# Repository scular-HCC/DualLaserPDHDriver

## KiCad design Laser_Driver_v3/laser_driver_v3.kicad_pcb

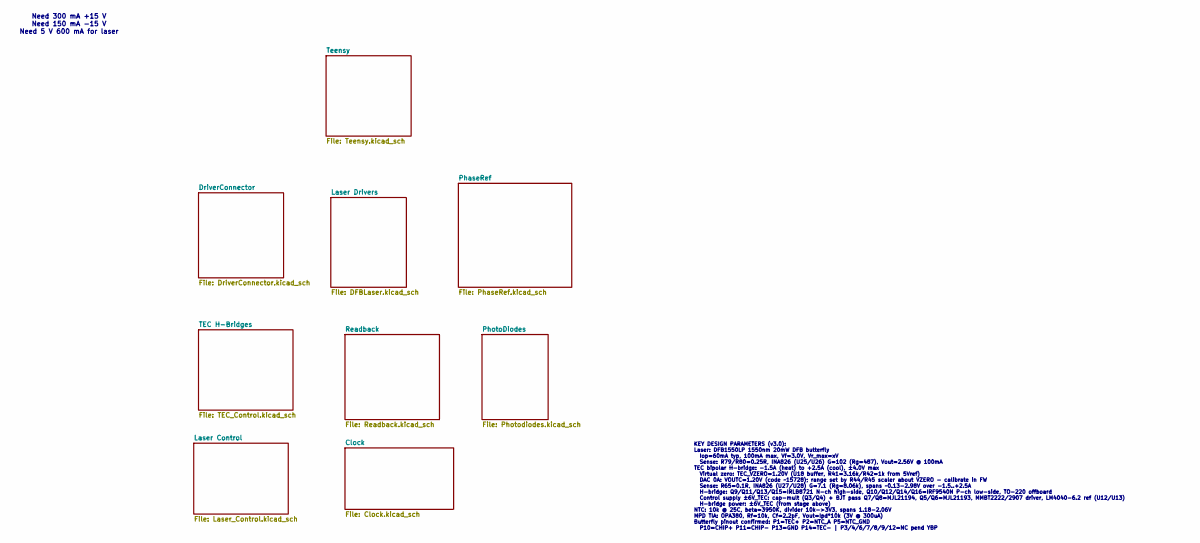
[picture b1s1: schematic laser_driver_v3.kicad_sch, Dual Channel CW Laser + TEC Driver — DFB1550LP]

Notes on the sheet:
Need 300 mA +15 V Need 150 mA -15 V Need 5 V 600 mA for laser
KEY DESIGN PARAMETERS (v3.0): Laser: DFB1550LP 1550nm 20mW DFB butterfly Iop=60mA typ, 100mA max, Vf=3.0V, Vr_max=xV Sense: R79/R80=0.25R, INA826 (U25/U26) G=102 (Rg=487), Vout=2.56V @ 100mA TEC bipolar H-bridge: -1.5A (heat) to +2.5A (cool), ±4.0V max Virtual zero: TEC_VZERO=1.20V (U18 buffer, R41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

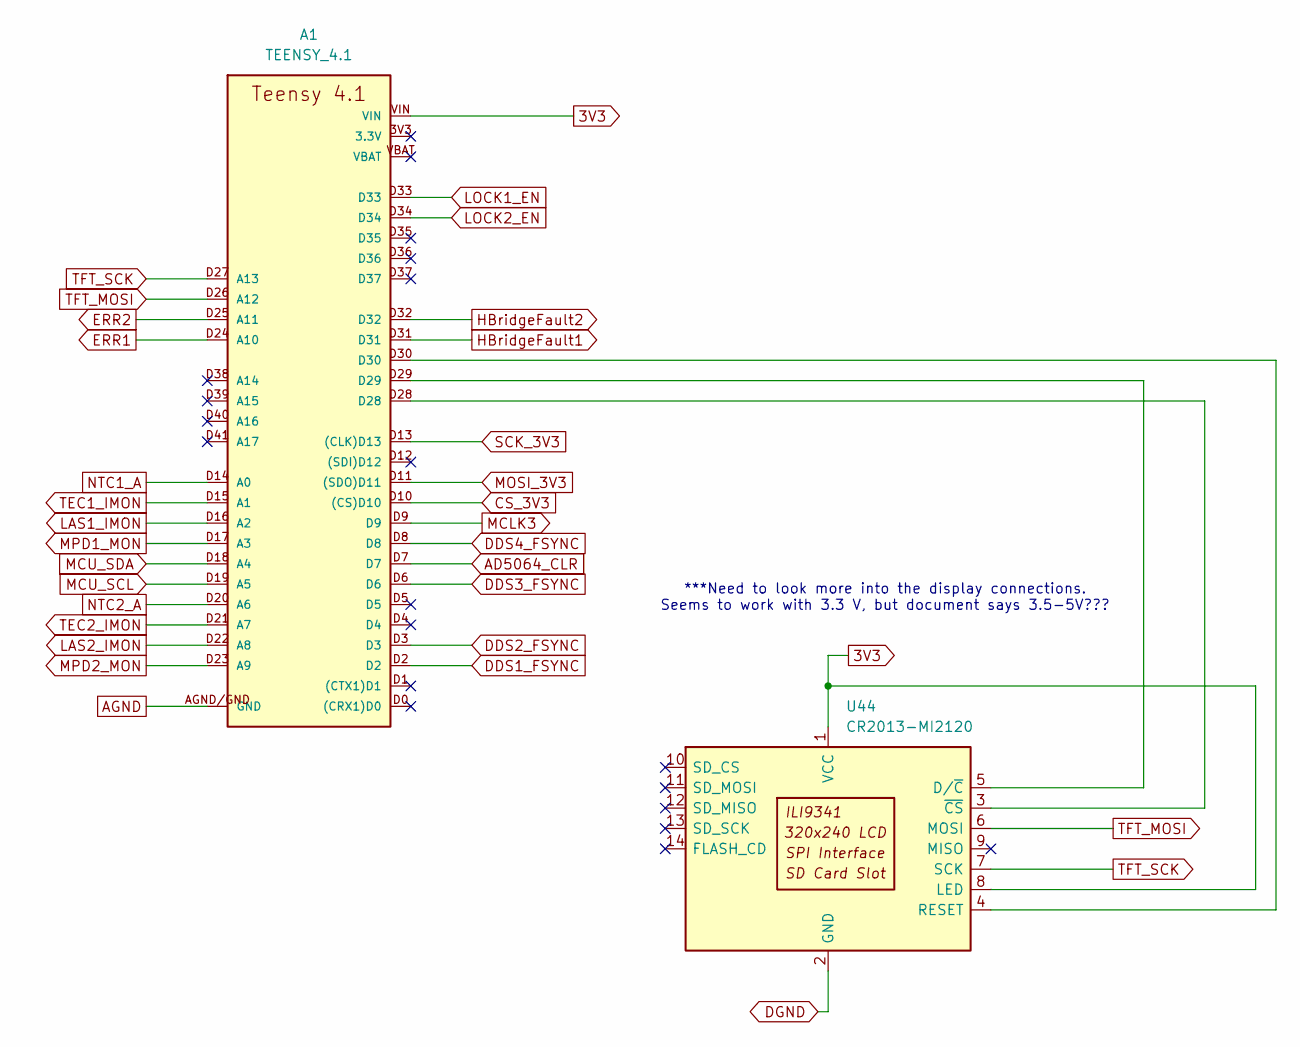
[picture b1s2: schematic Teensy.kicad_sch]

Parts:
A1: TEENSY_4.1; TEENSY_LONG_EXT
U44: CR2013-MI2120

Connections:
3V3: A1.VIN, U44.1 (VCC), U44.8 (LED); also elsewhere on the board
AD5064_CLR: A1.D7; also elsewhere on the board
AGND: A1.AGND/GND (GND), A1.GND, A1.GND@2 (GND); also elsewhere on the board
CS_3V3: A1.D10 ((CS)D10); also elsewhere on the board
DDS1_FSYNC: A1.D2; also elsewhere on the board
DDS2_FSYNC: A1.D3; also elsewhere on the board
DDS3_FSYNC: A1.D6; also elsewhere on the board
DDS4_FSYNC: A1.D8; also elsewhere on the board
DGND: U44.2 (GND); also elsewhere on the board
ERR1: A1.D24 (A10); also elsewhere on the board
ERR2: A1.D25 (A11); also elsewhere on the board
HBridgeFault1: A1.D31; also elsewhere on the board
HBridgeFault2: A1.D32; also elsewhere on the board
LAS1_IMON: A1.D16 (A2); also elsewhere on the board
LAS2_IMON: A1.D22 (A8); also elsewhere on the board
LOCK1_EN: A1.D33; also elsewhere on the board
LOCK2_EN: A1.D34; also elsewhere on the board
MCLK3: A1.D9; also elsewhere on the board
MCU_SCL: A1.D19 (A5); also elsewhere on the board
MCU_SDA: A1.D18 (A4); also elsewhere on the board
MOSI_3V3: A1.D11 ((SDO)D11); also elsewhere on the board
MPD1_MON: A1.D17 (A3); also elsewhere on the board
MPD2_MON: A1.D23 (A9); also elsewhere on the board
NTC1_A: A1.D14 (A0); also elsewhere on the board
NTC2_A: A1.D20 (A6); also elsewhere on the board
unnamed: A1.D29, U44.5 (D/~C)
unnamed: A1.D30, U44.4 (RESET)
unnamed: A1.D28, U44.3 (~CS)
SCK_3V3: A1.D13 ((CLK)D13); also elsewhere on the board
TEC1_IMON: A1.D15 (A1); also elsewhere on the board
TEC2_IMON: A1.D21 (A7); also elsewhere on the board
TFT_MOSI: A1.D26 (A12), U44.6 (MOSI)
TFT_SCK: A1.D27 (A13), U44.7 (SCK)

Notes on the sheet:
***Need to look more into the display connections. Seems to work with 3.3 V, but document says 3.5-5V???

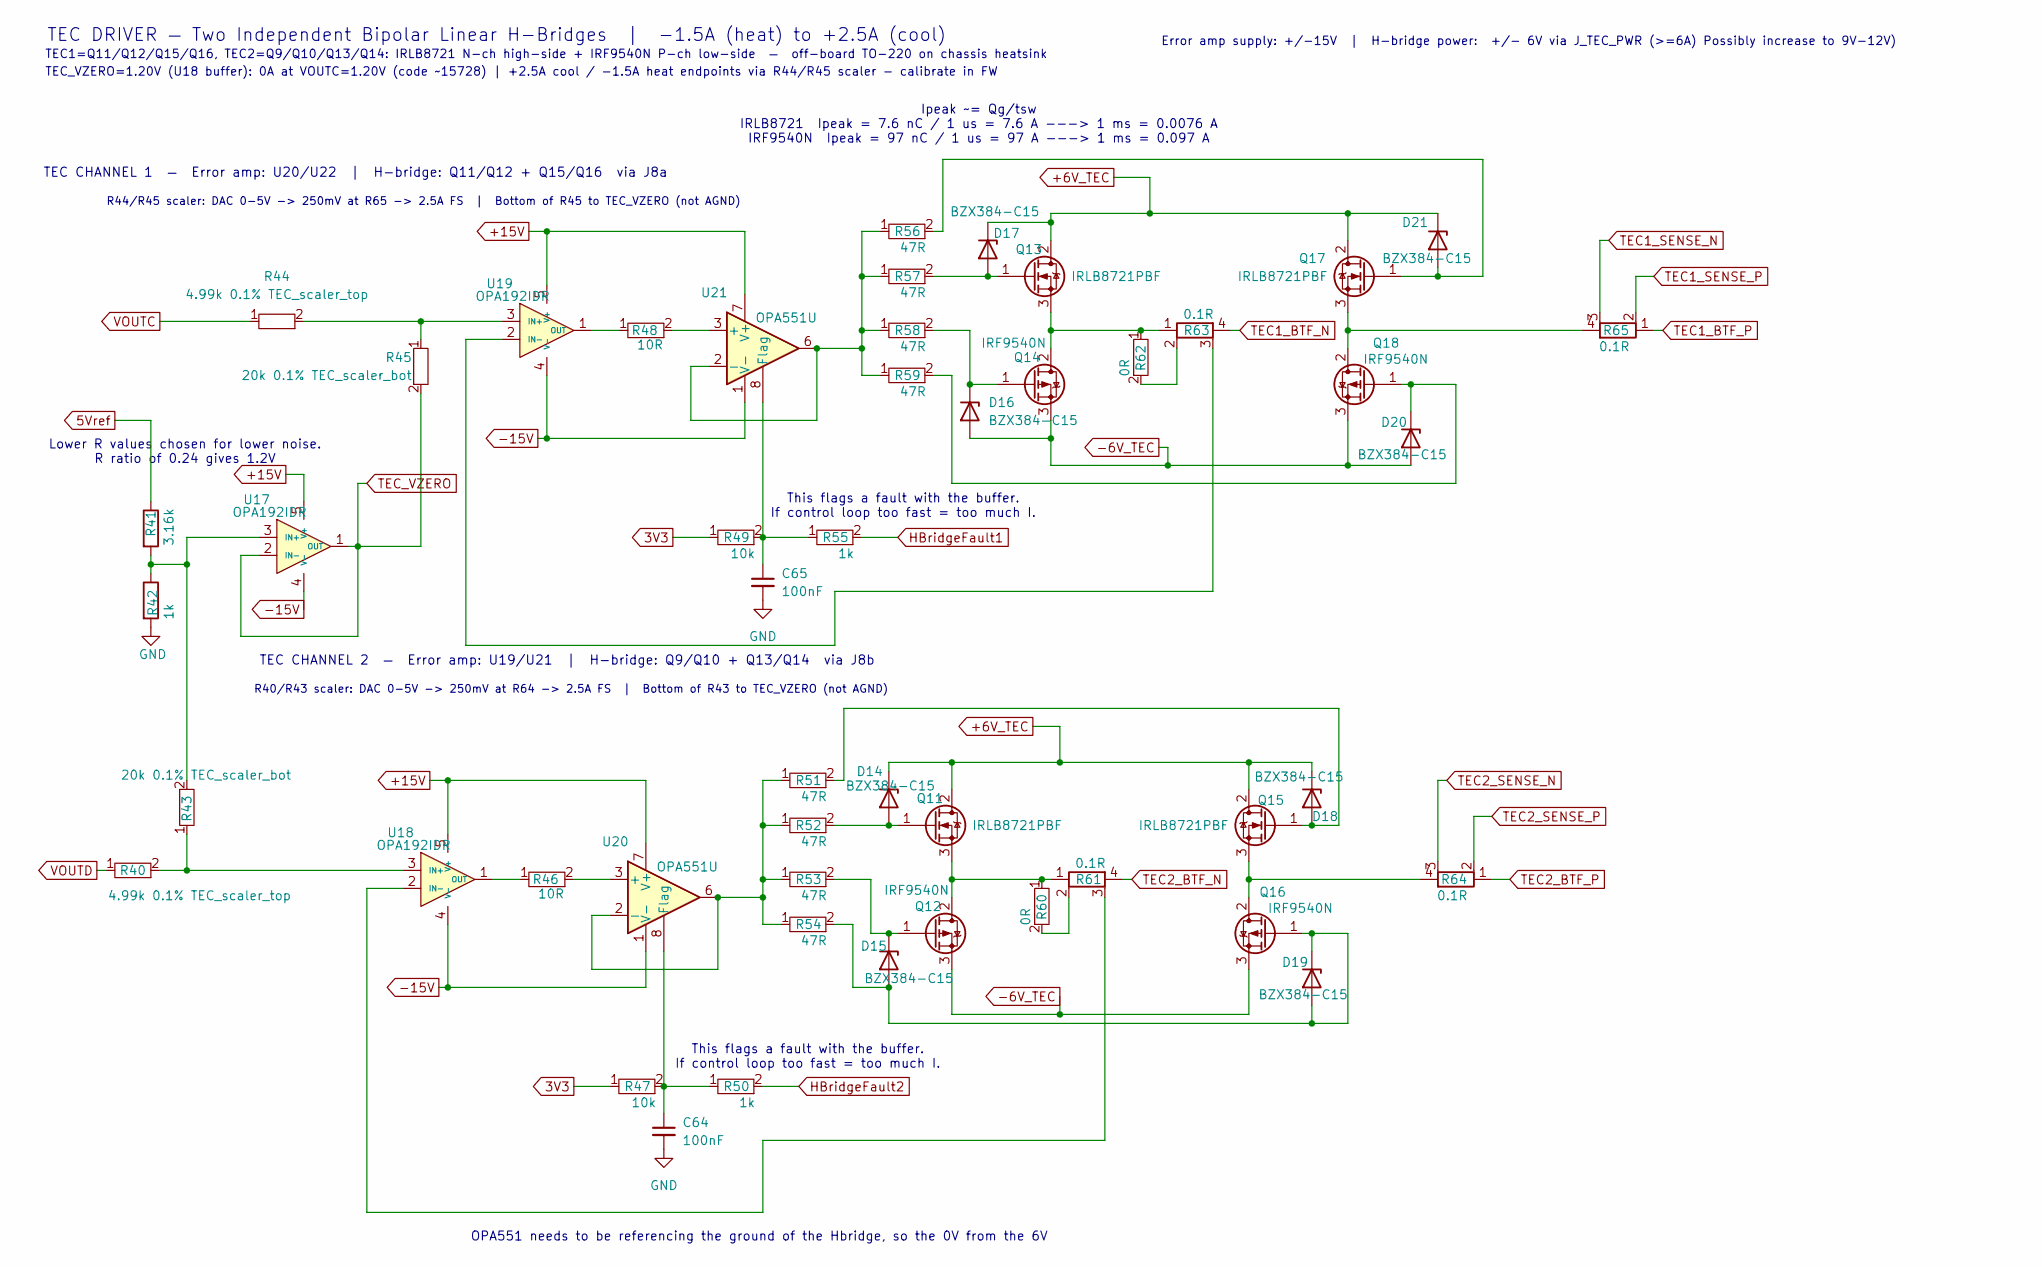
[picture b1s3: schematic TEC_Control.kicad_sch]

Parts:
C64, C65: 100nF; C_0805_2012Metric_Pad1.18x1.45mm_HandSolder
D14, D15, D16, D17, D18, D19, D20, D21: BZX384-C15; D_SOD-323
Q11, Q13, Q15, Q17: IRLB8721PBF; TO-220-3_Vertical
Q12, Q14, Q16, Q18: IRF9540N; TO-220-3_Vertical
R40, R44: 4.99k 0.1% TEC_scaler_top; R_0805_2012Metric
R41: 3.16k; R_0805_2012Metric_Pad1.20x1.40mm_HandSolder
R42, R50, R55: 1k; R_0805_2012Metric_Pad1.20x1.40mm_HandSolder
R43, R45: 20k 0.1% TEC_scaler_bot; R_0805_2012Metric
R46, R48: 10R; R_0805_2012Metric_Pad1.20x1.40mm_HandSolder
R47, R49: 10k; R_0805_2012Metric_Pad1.20x1.40mm_HandSolder
R51, R52, R53, R54, R56, R57, R58, R59: 47R; R_0805_2012Metric_Pad1.20x1.40mm_HandSolder
R60, R62: 0R; R_0805_2012Metric_Pad1.20x1.40mm_HandSolder
R61, R63, R64, R65: 0.1R; R_Shunt_Vishay_WSKW0612
U17, U18, U19: OPA192IDR; SOIC-8_3.9x4.9mm_P1.27mm
U20, U21: OPA551U; SOIC-8_3.9x4.9mm_P1.27mm

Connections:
3V3: R47.1, R49.1; also elsewhere on the board
5Vref: R41.1; also elsewhere on the board
+6V_TEC: D14.1 (K), D17.1 (K), D18.1 (K), D21.1 (K), Q11.2 (D), Q13.2 (D), Q15.2 (D), Q17.2 (D); also elsewhere on the board
+15V: U17.5 (V+), U18.5 (V+), U19.5 (V+), U20.7 (V+), U21.7 (V+); also elsewhere on the board
-6V_TEC: D16.2 (A), D20.2 (A), Q12.3 (S), Q14.3 (S), Q16.3 (S), Q18.3 (S); also elsewhere on the board
-15V: U17.4 (V-), U18.4 (V-), U19.4 (V-), U20.1 (V-), U20.4 (V-), U20.5 (V-), U21.1 (V-), U21.4 (V-), U21.5 (V-); also elsewhere on the board
GND: C64.2, C65.2, R42.2; also elsewhere on the board
HBridgeFault1: R55.2; also elsewhere on the board
HBridgeFault2: R50.2; also elsewhere on the board
unnamed: D14.2 (A), Q11.1 (G), R52.2
unnamed: D15.2 (A), D19.1 (K), D19.2 (A), Q16.1 (G), R54.2
unnamed: D15.1 (K), Q12.1 (G), R53.2
unnamed: D16.1 (K), Q14.1 (G), R58.2
unnamed: D17.2 (A), Q13.1 (G), R57.2
unnamed: D18.2 (A), Q15.1 (G), R51.2
unnamed: D20.1 (K), Q18.1 (G), R59.2
unnamed: D21.2 (A), Q17.1 (G), R56.2
unnamed: Q11.3 (S), Q12.2 (D), R60.1, R61.1
unnamed: Q13.3 (S), Q14.2 (D), R62.1, R63.1
unnamed: Q15.3 (S), Q16.2 (D), R64.4
unnamed: Q17.3 (S), Q18.2 (D), R65.4
unnamed: R60.2, R61.2
unnamed: R62.2, R63.2
unnamed: R41.2, R42.1, R43.2, U17.3 (IN+)
unnamed: R40.2, R43.1, U18.3 (IN+)
unnamed: R61.3, U18.2 (IN-)
unnamed: R46.1, U18.1 (OUT)
unnamed: R44.2, R45.1, U19.3 (IN+)
unnamed: R63.3, U19.2 (IN-)
unnamed: R48.1, U19.1 (OUT)
unnamed: R46.2, U20.3 (+)
unnamed: R51.1, R52.1, R53.1, R54.1, U20.2 (-), U20.6
unnamed: C64.1, R47.2, R50.1, U20.8 (Flag)
unnamed: R48.2, U21.3 (+)
unnamed: R56.1, R57.1, R58.1, R59.1, U21.2 (-), U21.6
unnamed: C65.1, R49.2, R55.1, U21.8 (Flag)
TEC1_BTF_N: R63.4; also elsewhere on the board
TEC1_BTF_P: R65.1; also elsewhere on the board
TEC1_SENSE_N: R65.3; also elsewhere on the board
TEC1_SENSE_P: R65.2; also elsewhere on the board
TEC2_BTF_N: R61.4; also elsewhere on the board
TEC2_BTF_P: R64.1; also elsewhere on the board
TEC2_SENSE_N: R64.3; also elsewhere on the board
TEC2_SENSE_P: R64.2; also elsewhere on the board
TEC_VZERO: R45.2, U17.1 (OUT), U17.2 (IN-); also elsewhere on the board
VOUTC: R44.1; also elsewhere on the board
VOUTD: R40.1; also elsewhere on the board

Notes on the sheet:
TEC1=Q11/Q12/Q15/Q16, TEC2=Q9/Q10/Q13/Q14: IRLB8721 N-ch high-side + IRF9540N P-ch low-side — off-board TO-220 on chassis heatsink
OPA551 needs to be referencing the ground of the Hbridge, so the 0V from the 6V
TEC CHANNEL 2 — Error amp: U19/U21 | H-bridge: Q9/Q10 + Q13/Q14 via J8b
R44/R45 scaler: DAC 0-5V -> 250mV at R65 -> 2.5A FS | Bottom of R45 to TEC_VZERO (not AGND)
TEC_VZERO=1.20V (U18 buffer): 0A at VOUTC=1.20V (code ~15728) | +2.5A cool / -1.5A heat endpoints via R44/R45 scaler - calibrate in FW
R40/R43 scaler: DAC 0-5V -> 250mV at R64 -> 2.5A FS | Bottom of R43 to TEC_VZERO (not AGND)
This flags a fault with the buffer. If control loop too fast = too much I.
Ipeak ~= Qg/tsw IRLB8721 Ipeak = 7.6 nC / 1 us = 7.6 A ---> 1 ms = 0.0076 A IRF9540N Ipeak = 97 nC / 1 us = 97 A ---> 1 ms = 0.097 A
TEC CHANNEL 1 — Error amp: U20/U22 | H-bridge: Q11/Q12 + Q15/Q16 via J8a
Lower R values chosen for lower noise. R ratio of 0.24 gives 1.2V
Error amp supply: +/-15V | H-bridge power: +/- 6V via J_TEC_PWR (>=6A) Possibly increase to 9V-12V)
TEC DRIVER — Two Independent Bipolar Linear H-Bridges | -1.5A (heat) to +2.5A (cool)

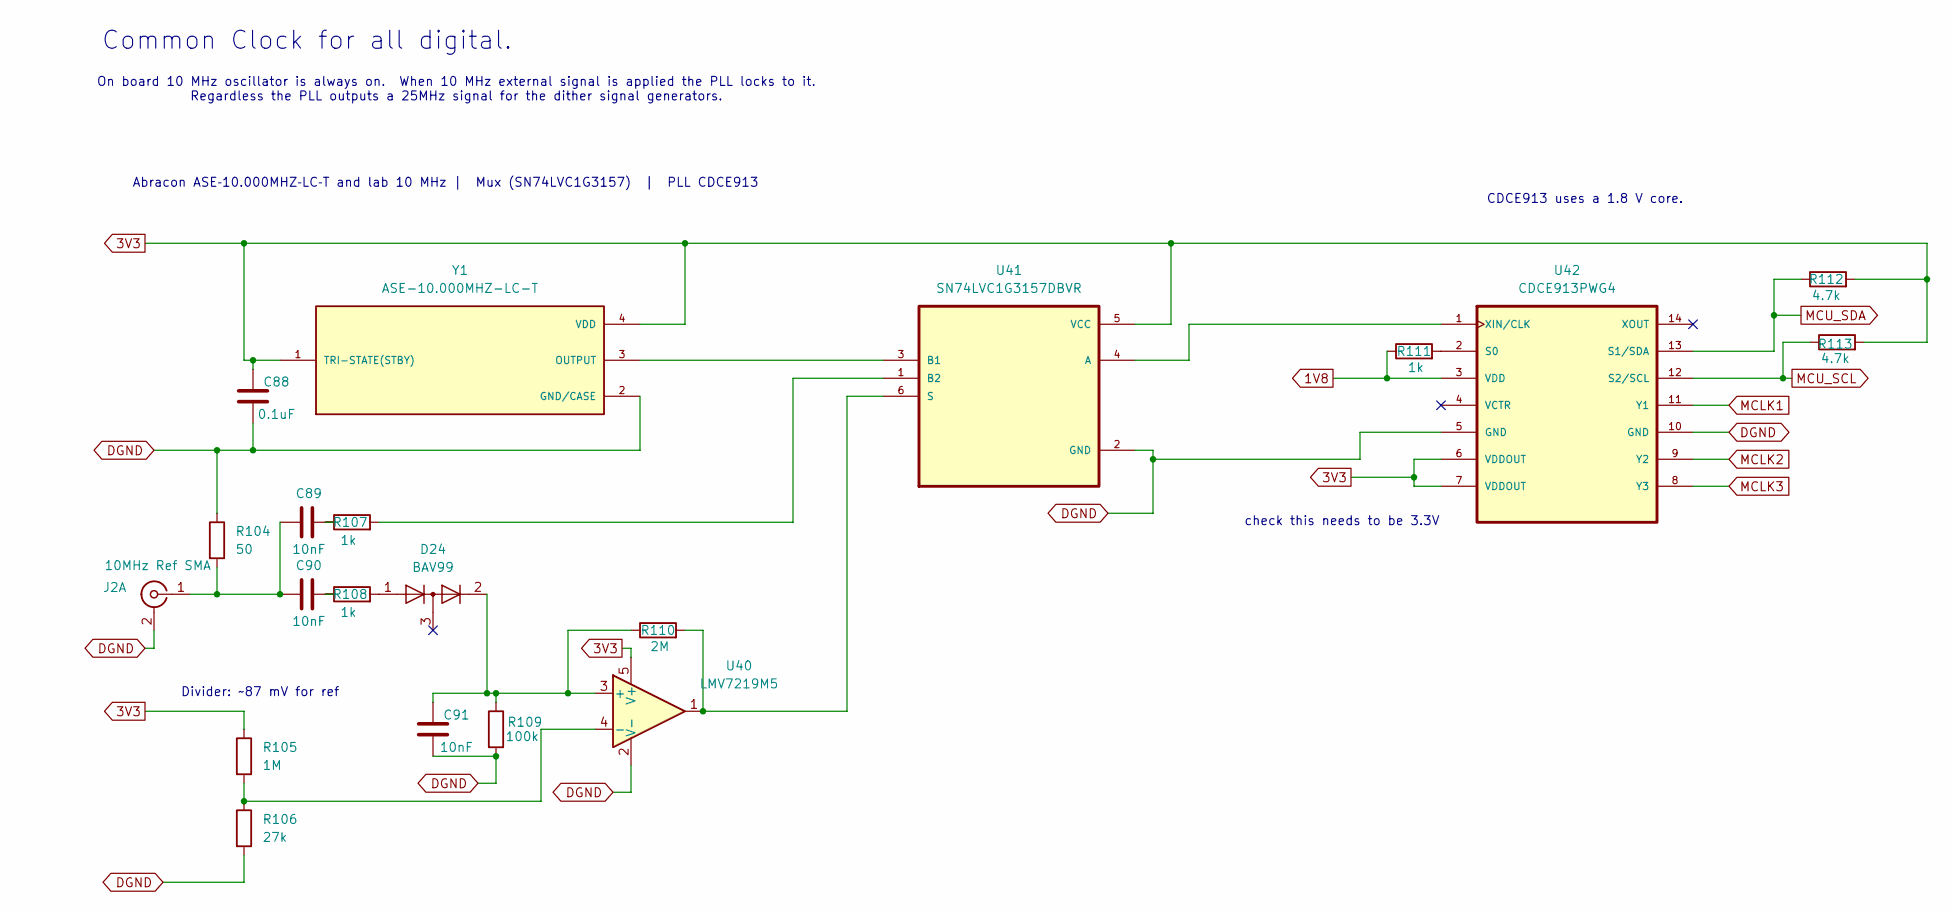
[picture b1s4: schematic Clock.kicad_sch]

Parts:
C88: 0.1uF; C_0805_2012Metric_Pad1.18x1.45mm_HandSolder
C89, C90, C91: 10nF; C_0805_2012Metric_Pad1.18x1.45mm_HandSolder
D24: BAV99; SOT-23
J2: 10MHz Ref SMA; SMA_BAT_Wireless_BWSMA-KWE-Z001
R104: 50; R_0805_2012Metric_Pad1.20x1.40mm_HandSolder
R105: 1M; R_0805_2012Metric_Pad1.20x1.40mm_HandSolder
R106: 27k; R_0805_2012Metric_Pad1.20x1.40mm_HandSolder
R107, R108, R111: 1k; R_0805_2012Metric_Pad1.20x1.40mm_HandSolder
R109: 100k; R_0805_2012Metric_Pad1.20x1.40mm_HandSolder
R110: 2M; R_0805_2012Metric_Pad1.20x1.40mm_HandSolder
R112, R113: 4.7k; R_0805_2012Metric_Pad1.20x1.40mm_HandSolder
U40: LMV7219M5; SOT-23-5
U41: SN74LVC1G3157DBVR; SOT-23-6_Handsoldering
U42: CDCE913PWG4; SOP65P640X120-14N
Y1: ASE-10.000MHZ-LC-T; XTAL_ASE-10.000MHZ-LC-T; PARTREV 02-18-22

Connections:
1V8: R111.1, U42.3 (VDD); also elsewhere on the board
3V3: C88.2, R105.1, R112.2, R113.2, U40.5 (V+), U41.5 (VCC), U42.6 (VDDOUT), U42.7 (VDDOUT), Y1.1 (TRI-STATE(STBY)), Y1.4 (VDD); also elsewhere on the board
DGND: C88.1, C91.1, J2.2 (Ext1), R104.1, R106.2, R109.2, U40.2 (V-), U41.2 (GND), U42.5 (GND), U42.10 (GND), Y1.2 (GND/CASE); also elsewhere on the board
MCLK1: U42.11 (Y1); also elsewhere on the board
MCLK2: U42.9 (Y2); also elsewhere on the board
MCLK3: U42.8 (Y3); also elsewhere on the board
MCU_SCL: R113.1, U42.12 (S2/SCL); also elsewhere on the board
MCU_SDA: R112.1, U42.13 (S1/SDA); also elsewhere on the board
unnamed: C89.2, R107.1
unnamed: C90.2, R108.1
unnamed: C91.2, D24.2 (A), R109.1, R110.1, U40.3 (+)
unnamed: D24.1 (K), R108.2
unnamed: C89.1, C90.1, J2.1 (In1), R104.2
unnamed: R105.2, R106.1, U40.4 (-)
unnamed: U41.4 (A), U42.1 (XIN/CLK)
unnamed: U41.3 (B1), Y1.3 (OUTPUT)
unnamed: R107.2, U41.1 (B2)
unnamed: R110.2, U40.1, U41.6 (S)
unnamed: R111.2, U42.2 (S0)

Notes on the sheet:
Divider: ~87 mV for ref
CDCE913 uses a 1.8 V core.
check this needs to be 3.3V
Common Clock for all digital.
Abracon ASE‑10.000MHZ‑LC‑T and lab 10 MHz | Mux (SN74LVC1G3157) | PLL CDCE913
On board 10 MHz oscillator is always on. When 10 MHz external signal is applied the PLL locks to it. Regardless the PLL outputs a 25MHz signal for the dither signal generators.

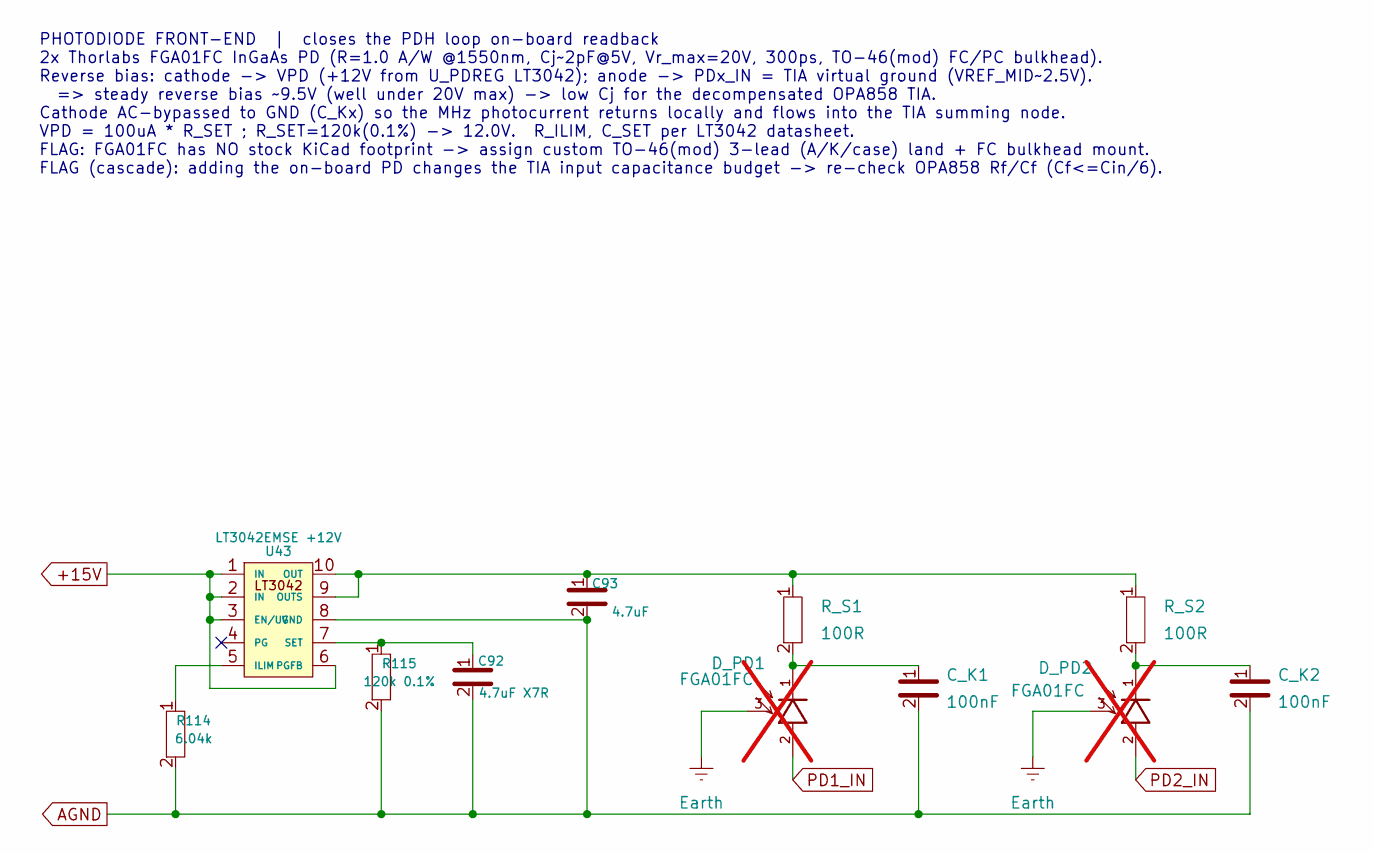
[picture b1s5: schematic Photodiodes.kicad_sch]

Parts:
C92: 4.7uF X7R; C_0805_2012Metric_Pad1.18x1.45mm_HandSolder
C93: 4.7uF; C_0805_2012Metric_Pad1.18x1.45mm_HandSolder
C_K1, C_K2: 100nF; C_0805_2012Metric_Pad1.18x1.45mm_HandSolder
D_PD1, D_PD2: FGA01FC; not fitted
R114: 6.04k; R_0805_2012Metric_Pad1.20x1.40mm_HandSolder
R115: 120k 0.1%; R_0805_2012Metric_Pad1.20x1.40mm_HandSolder
R_S1, R_S2: 100R; R_0805_2012Metric_Pad1.20x1.40mm_HandSolder
U43: LT3042EMSE +12V; MSOP-10-1EP_3x3mm_P0.5mm_EP2.2x3.1mm_Mask1.83x1.89mm_Therma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

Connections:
+15V: U43.1 (IN), U43.2 (IN), U43.3 (EN/UV), U43.6 (PGFB); also elsewhere on the board
AGND: C92.2, C93.2, C_K1.2, C_K2.2, R114.2, R115.2, U43.8 (GND); also elsewhere on the board
unnamed: C_K1.1, D_PD1.1 (K), R_S1.2
unnamed: C_K2.1, D_PD2.1 (K), R_S2.2
unnamed: D_PD1.3 (CASE), D_PD2.3 (CASE)
unnamed: R114.1, U43.5 (ILIM)
unnamed: C93.1, R_S1.1, R_S2.1, U43.9 (OUTS), U43.10 (OUT)
unnamed: C92.1, R115.1, U43.7 (SET)

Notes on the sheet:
PHOTODIODE FRONT-END | closes the PDH loop on-board readback 2x Thorlabs FGA01FC InGaAs PD (R=1.0 A/W @1550nm, Cj~2pF@5V, Vr_max=20V, 300ps, TO-46(mod) FC/PC bulkhead). Reverse bias: cathode -> VPD (+12V from U_PDREG LT3042); anode -> PDx_IN = TIA virtual ground (VREF_MID~2.5V). => steady reverse b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

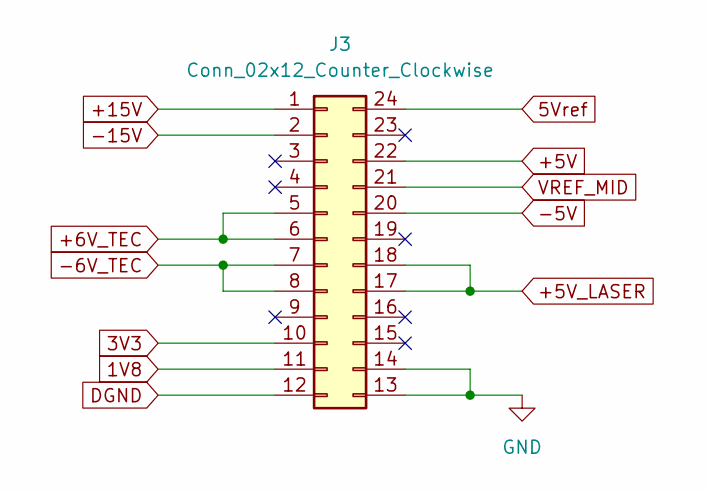
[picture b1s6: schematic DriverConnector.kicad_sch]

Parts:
J3: Conn_02x12_Counter_Clockwise; Molex_Micro-Fit_3.0_43045-2412_2x12_P3.00mm_Vertical

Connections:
1V8: J3.11; also elsewhere on the board
3V3: J3.10; also elsewhere on the board
5Vref: J3.24; also elsewhere on the board
+5V: J3.22; also elsewhere on the board
+5V_LASER: J3.17, J3.18; also elsewhere on the board
+6V_TEC: J3.5, J3.6; also elsewhere on the board
+15V: J3.1; also elsewhere on the board
-5V: J3.20; also elsewhere on the board
-6V_TEC: J3.7, J3.8; also elsewhere on the board
-15V: J3.2; also elsewhere on the board
DGND: J3.12; also elsewhere on the board
GND: J3.13, J3.14; also elsewhere on the board
VREF_MID: J3.21; also elsewhere on the board

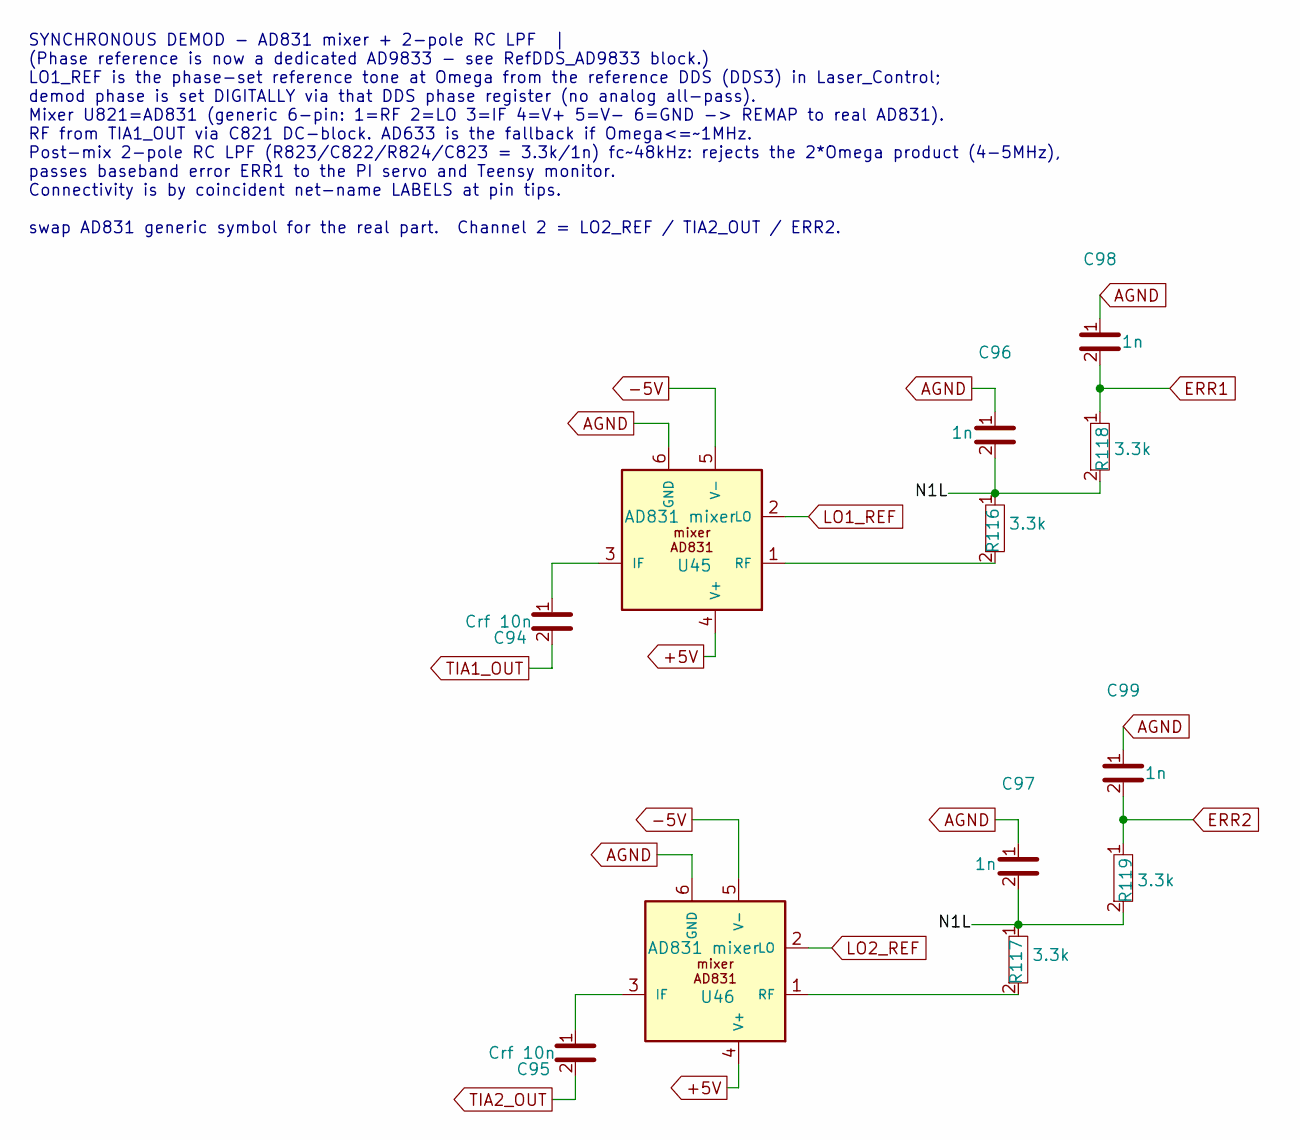
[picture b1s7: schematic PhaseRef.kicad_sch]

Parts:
C94, C95: Crf 10n; C_0805_2012Metric_Pad1.18x1.45mm_HandSolder
C96, C97, C98, C99: 1n; C_0805_2012Metric_Pad1.18x1.45mm_HandSolder
R116, R117, R118, R119: 3.3k; R_0805_2012Metric_Pad1.20x1.40mm_HandSolder
U45, U46: AD831 mixer; PLCC20S

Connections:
+5V: U45.4 (V+), U46.4 (V+); also elsewhere on the board
-5V: U45.5 (V-), U46.5 (V-); also elsewhere on the board
/PhaseRef/N1L: C96.2, C97.2, R116.1, R117.1, R118.2, R119.2
AGND: C96.1, C97.1, C98.1, C99.1, U45.6 (GND), U46.6 (GND); also elsewhere on the board
ERR1: C98.2, R118.1; also elsewhere on the board
ERR2: C99.2, R119.1; also elsewhere on the board
LO1_REF: U45.2 (LO); also elsewhere on the board
LO2_REF: U46.2 (LO); also elsewhere on the board
unnamed: C94.1, U45.3 (IF)
unnamed: R116.2, U45.1 (RF)
unnamed: C95.1, U46.3 (IF)
unnamed: R117.2, U46.1 (RF)
TIA1_OUT: C94.2; also elsewhere on the board
TIA2_OUT: C95.2; also elsewhere on the board

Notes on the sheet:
SYNCHRONOUS DEMOD - AD831 mixer + 2-pole RC LPF | (Phase reference is now a dedicated AD9833 - see RefDDS_AD9833 block.) LO1_REF is the phase-set reference tone at Omega from the reference DDS (DDS3) in Laser_Control; demod phase is set DIGITALLY via that DDS phase register (no analog all-pass). Mi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

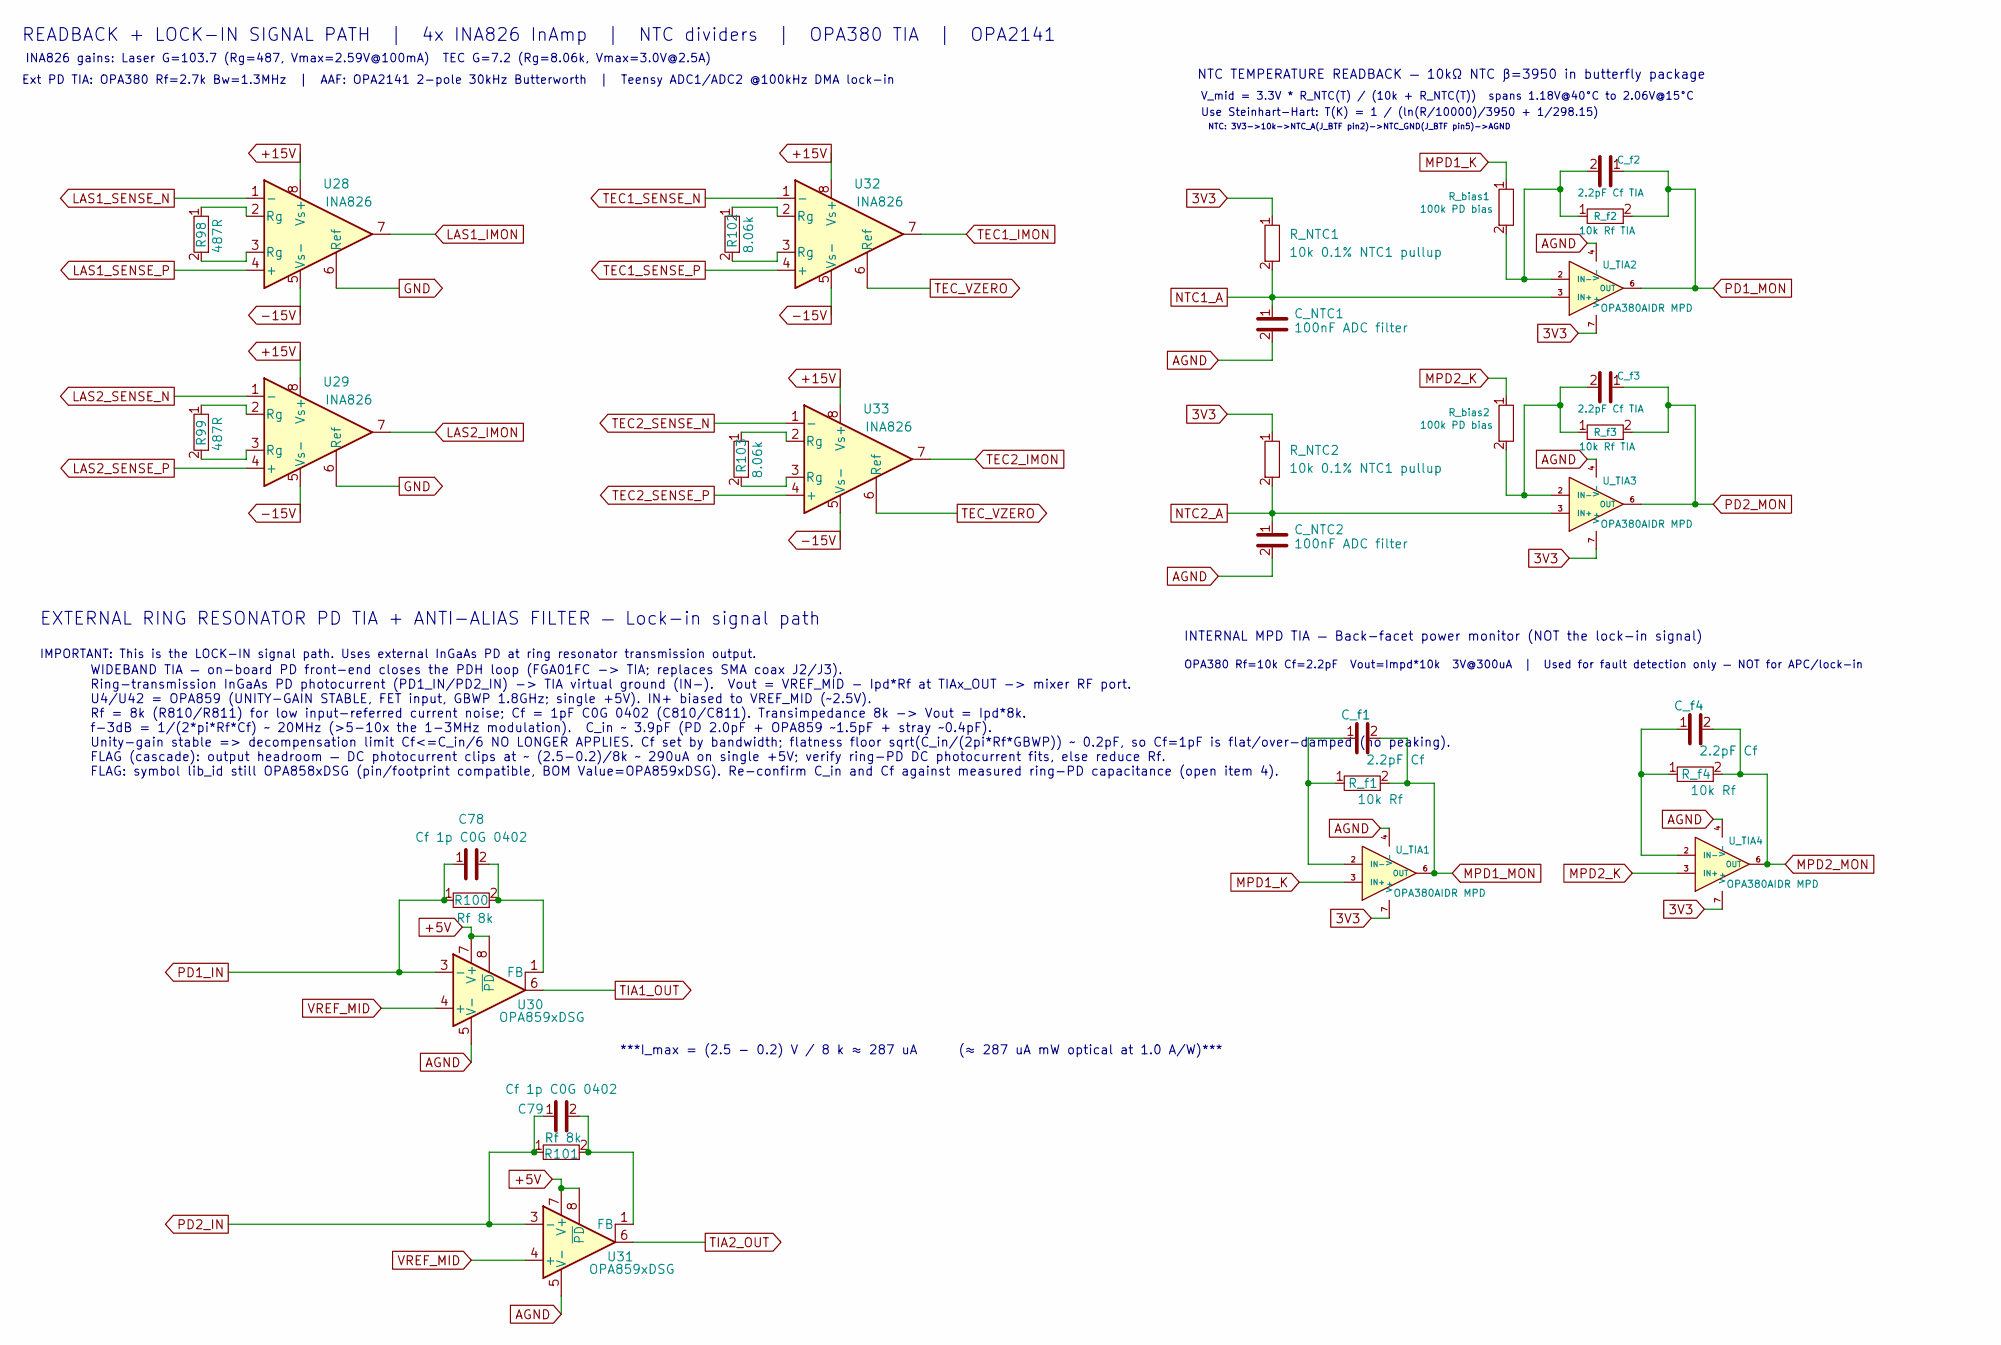
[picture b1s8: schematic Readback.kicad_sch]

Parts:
C78: Cf 1p C0G 0402; C_0402_1005Metric_Pad0.74x0.62mm_HandSolder
C79: Cf 1p C0G 0402; R_0805_2012Metric_Pad1.20x1.40mm_HandSolder
C_NTC1, C_NTC2: 100nF ADC filter; C_0805_2012Metric_Pad1.18x1.45mm_HandSolder
C_f1, C_f4: 2.2pF Cf; C_0402_1005Metric
C_f2, C_f3: 2.2pF Cf TIA; C_0402_1005Metric
R98, R99: 487R; R_0805_2012Metric_Pad1.20x1.40mm_HandSolder
R100, R101: Rf 8k; R_0805_2012Metric_Pad1.20x1.40mm_HandSolder
R102, R103: 8.06k; R_0805_2012Metric_Pad1.20x1.40mm_HandSolder
R_NTC1, R_NTC2: 10k 0.1% NTC1 pullup; R_0805_2012Metric
R_bias1, R_bias2: 100k PD bias; R_0805_2012Metric_Pad1.20x1.40mm_HandSolder
R_f1, R_f4: 10k Rf; R_0805_2012Metric_Pad1.20x1.40mm_HandSolder
R_f2, R_f3: 10k Rf TIA; R_0805_2012Metric_Pad1.20x1.40mm_HandSolder
U28, U29, U32, U33: INA826; SOIC-8_3.9x4.9mm_P1.27mm
U30, U31: OPA859xDSG; WSON-8-1EP_2x2mm_P0.5mm_EP0.9x1.6mm
U_TIA1, U_TIA2, U_TIA3, U_TIA4: OPA380AIDR MPD; SOIC-8_3.9x4.9mm_P1.27mm

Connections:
3V3: R_NTC1.1, R_NTC2.1, U_TIA1.7 (V+), U_TIA2.7 (V+), U_TIA3.7 (V+), U_TIA4.7 (V+); also elsewhere on the board
+5V: U30.7 (V+), U30.8 (~PD), U31.7 (V+), U31.8 (~PD); also elsewhere on the board
+15V: U28.8 (Vs+), U29.8 (Vs+), U32.8 (Vs+), U33.8 (Vs+); also elsewhere on the board
-15V: U28.5 (Vs-), U29.5 (Vs-), U32.5 (Vs-), U33.5 (Vs-); also elsewhere on the board
AGND: C_NTC1.2, C_NTC2.2, U30.5 (V-), U30.9 (V-), U31.5 (V-), U31.9 (V-), U_TIA1.4 (V-), U_TIA2.4 (V-), U_TIA3.4 (V-), U_TIA4.4 (V-); also elsewhere on the board
GND: U28.6 (Ref), U29.6 (Ref); also elsewhere on the board
LAS1_IMON: U28.7; also elsewhere on the board
LAS1_SENSE_N: U28.1 (-); also elsewhere on the board
LAS1_SENSE_P: U28.4 (+); also elsewhere on the board
LAS2_IMON: U29.7; also elsewhere on the board
LAS2_SENSE_N: U29.1 (-); also elsewhere on the board
LAS2_SENSE_P: U29.4 (+); also elsewhere on the board
MPD1_K: R_bias1.1, U_TIA1.3 (IN+)
MPD1_MON: C_f1.2, R_f1.2, U_TIA1.6 (OUT); also elsewhere on the board
MPD2_K: R_bias2.1, U_TIA4.3 (IN+)
MPD2_MON: C_f4.2, R_f4.2, U_TIA4.6 (OUT); also elsewhere on the board
NTC1_A: C_NTC1.1, R_NTC1.2, U_TIA2.3 (IN+); also elsewhere on the board
NTC2_A: C_NTC2.1, R_NTC2.2, U_TIA3.3 (IN+); also elsewhere on the board
unnamed: R98.1, U28.2 (Rg)
unnamed: R98.2, U28.3 (Rg)
unnamed: R99.1, U29.2 (Rg)
unnamed: R99.2, U29.3 (Rg)
unnamed: R102.1, U32.2 (Rg)
unnamed: R102.2, U32.3 (Rg)
unnamed: R103.1, U33.2 (Rg)
unnamed: R103.2, U33.3 (Rg)
unnamed: C78.2, R100.2, U30.1 (FB)
unnamed: C79.2, R101.2, U31.1 (FB)
unnamed: C_f1.1, R_f1.1, U_TIA1.2 (IN-)
unnamed: C_f2.2, R_bias1.2, R_f2.1, U_TIA2.2 (IN-)
unnamed: C_f3.2, R_bias2.2, R_f3.1, U_TIA3.2 (IN-)
unnamed: C_f4.1, R_f4.1, U_TIA4.2 (IN-)
PD1_IN: C78.1, R100.1, U30.3 (-)
PD1_MON: C_f2.1, R_f2.2, U_TIA2.6 (OUT)
PD2_IN: C79.1, R101.1, U31.3 (-)
PD2_MON: C_f3.1, R_f3.2, U_TIA3.6 (OUT)
TEC1_IMON: U32.7; also elsewhere on the board
TEC1_SENSE_N: U32.1 (-); also elsewhere on the board
TEC1_SENSE_P: U32.4 (+); also elsewhere on the board
TEC2_IMON: U33.7; also elsewhere on the board
TEC2_SENSE_N: U33.1 (-); also elsewhere on the board
TEC2_SENSE_P: U33.4 (+); also elsewhere on the board
TEC_VZERO: U32.6 (Ref), U33.6 (Ref); also elsewhere on the board
TIA1_OUT: U30.6; also elsewhere on the board
TIA2_OUT: U31.6; also elsewhere on the board
VREF_MID: U30.4 (+), U31.4 (+); also elsewhere on the board

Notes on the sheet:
IMPORTANT: This is the LOCK-IN signal path. Uses external InGaAs PD at ring resonator transmission output.
READBACK + LOCK-IN SIGNAL PATH | 4x INA826 InAmp | NTC dividers | OPA380 TIA | OPA2141
NTC TEMPERATURE READBACK — 10kΩ NTC β=3950 in butterfly package
WIDEBAND TIA — on-board PD front-end closes the PDH loop (FGA01FC -> TIA; replaces SMA coax J2/J3). Ring-transmission InGaAs PD photocurrent (PD1_IN/PD2_IN) -> TIA virtual ground (IN-). Vout = VREF_MID - Ipd*Rf at TIAx_OUT -> mixer RF port. U4/U42 = OPA859 (UNITY-GAIN STABLE, FET input, GBWP 1.8GHz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
EXTERNAL RING RESONATOR PD TIA + ANTI-ALIAS FILTER — Lock-in signal path
Ext PD TIA: OPA380 Rf=2.7k Bw=1.3MHz | AAF: OPA2141 2-pole 30kHz Butterworth | Teensy ADC1/ADC2 @100kHz DMA lock-in
***I_max = (2.5 − 0.2) V / 8 k ≈ 287 uA (≈ 287 uA mW optical at 1.0 A/W)***
INA826 gains: Laser G=103.7 (Rg=487, Vmax=2.59V@100mA) TEC G=7.2 (Rg=8.06k, Vmax=3.0V@2.5A)
OPA380 Rf=10k Cf=2.2pF Vout=Impd*10k 3V@300uA | Used for fault detection only — NOT for APC/lock-in
Use Steinhart-Hart: T(K) = 1 / (ln(R/10000)/3950 + 1/298.15)
INTERNAL MPD TIA — Back-facet power monitor (NOT the lock-in signal)
NTC: 3V3->10k->NTC_A(J_BTF pin2)->NTC_GND(J_BTF pin5)->AGND
V_mid = 3.3V * R_NTC(T) / (10k + R_NTC(T)) spans 1.18V@40°C to 2.06V@15°C
